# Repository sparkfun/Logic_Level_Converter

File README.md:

**NOTE:** *This product has been retired from our catalog. For a more up-to-date version, try looking at the [bi-directional logic level converter](https://www.sparkfun.com/products/12009).*

*If you are looking for more up-to-date info, please check out some of these resources to see how other users are still hacking and improving on this product.*

* *[SparkFun Forum](https://forum.sparkfun.com/)*
* *[Comments Here on GitHub](https://github.com/sparkfun/Logic_Level_Converter/issues)*
* *[IRC Channel](https://www.sparkfun.com/news/263)*

Logic Level Converter
=====================

[*Logic Level Converter*](https://www.sparkfun.com/products/11978)

Design files for the [Logic Level Converter board](https://www.sparkfun.com/products/11978).

Repository Contents
-------------------

* **/hardware** - Eagle PCB layout files
* **/Production Files** - Files to support SparkFun production

Documentation
--------------
* **[Hookup Guide](https://learn.sparkfun.com/tutorials/retired---using-the-logic-level-converter)** - Basic hookup guide

License Information
-------------------

All contents of this repository are released under [Creative Commons Share-alike 3.0](http://creativecommons.org/licenses/by-sa/3.0/).

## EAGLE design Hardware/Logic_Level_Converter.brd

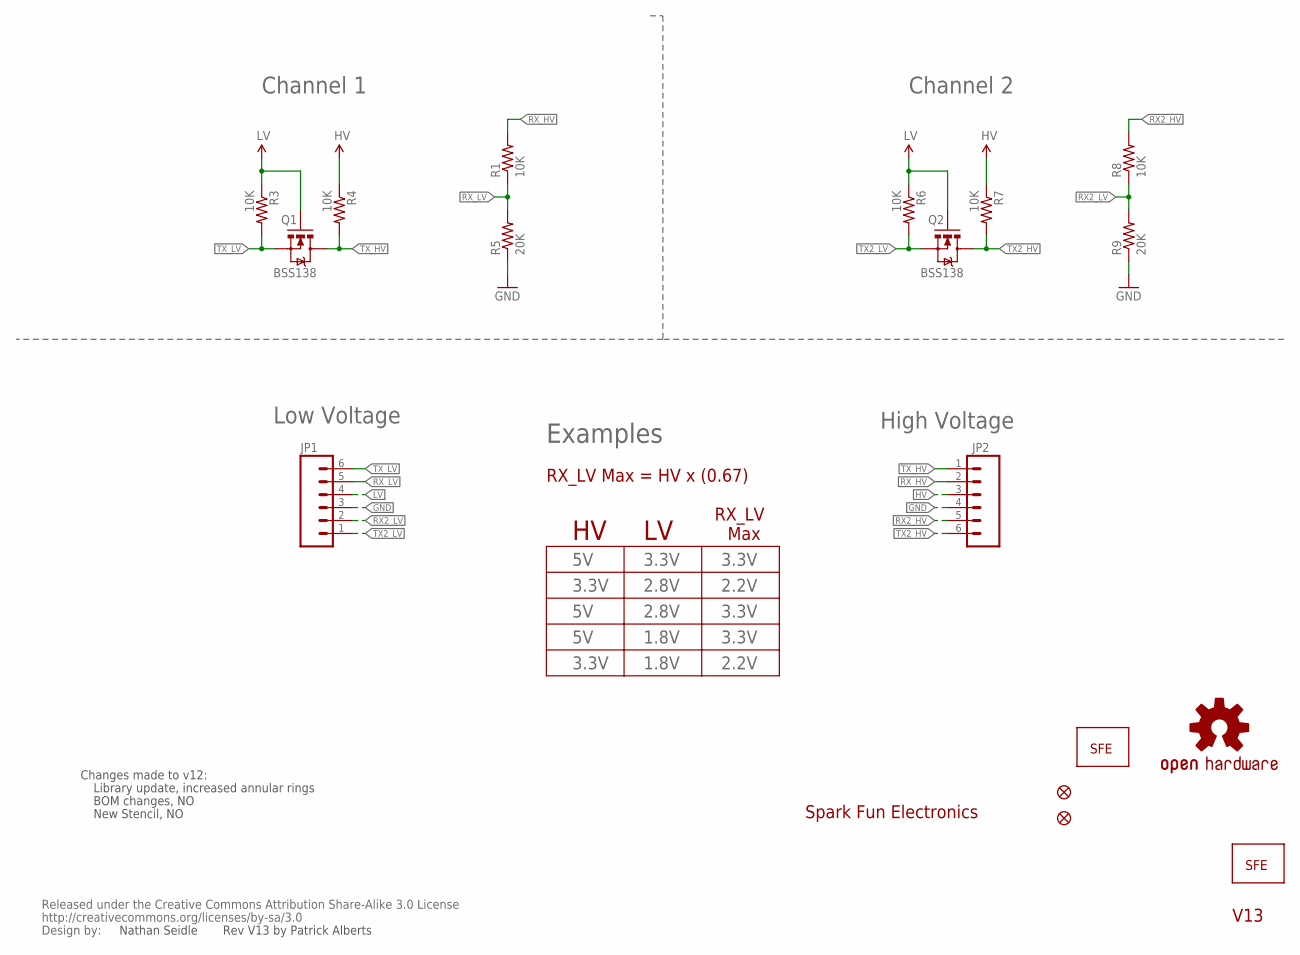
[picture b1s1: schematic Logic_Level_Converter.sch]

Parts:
CC_TEXT1: CREATIVE_COMMONS
JP1, JP2: M06SIP; 1X06
JP3, JP4: FIDUCIALUFIDUCIAL; MICRO-FIDUCIAL
JP5: LOGO-SFENW2; SFE-NEW-WEB
Q1, Q2: BSS138; SOT23-3
R1, R3, R4, R6, R7, R8: 10K; 0603-RES
R5, R9: 20K; 0603-RES
U$1: LOGO-SFESK; SFE-LOGO-FLAME
U$2: OSHW-LOGOS; OSHW-LOGO-S

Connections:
GND: JP1.3, JP2.4, R5.1, R9.1
HV: JP2.3, R4.1, R7.1
LV: JP1.4, Q1.1 (G), Q2.1 (G), R3.1, R6.1
RX2_HV: JP2.5, R8.2
RX2_LV: JP1.2, R8.1, R9.2
RX_HV: JP2.2, R1.2
RX_LV: JP1.5, R1.1, R5.2
TX2_HV: JP2.6, Q2.3 (D), R7.2
TX2_LV: JP1.1, Q2.2 (S), R6.2
TX_HV: JP2.1, Q1.3 (D), R4.2
TX_LV: JP1.6, Q1.2 (S), R3.2

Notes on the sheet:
Spark Fun Electronics
Channel 1
Channel 2
High Voltage
Low Voltage
Examples
RX_LV
Max
3.3V
2.8V
2.2V
1.8V
Changes made to v12:
Library update, increased annular rings
BOM changes, NO
New Stencil, NO
V13
RX_LV Max = HV x (0.67)
Nathan Seidle
Rev V13 by Patrick Alberts

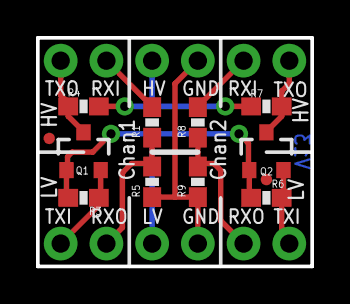
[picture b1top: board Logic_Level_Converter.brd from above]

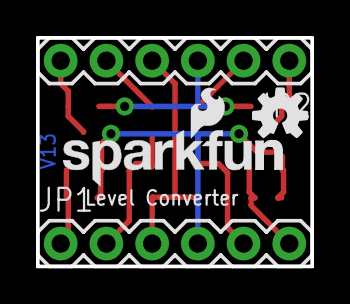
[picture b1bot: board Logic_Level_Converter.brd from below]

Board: 2 copper layers, 15.2 x 12.7 mm, 18 parts (5 on the bottom side), 11 nets.

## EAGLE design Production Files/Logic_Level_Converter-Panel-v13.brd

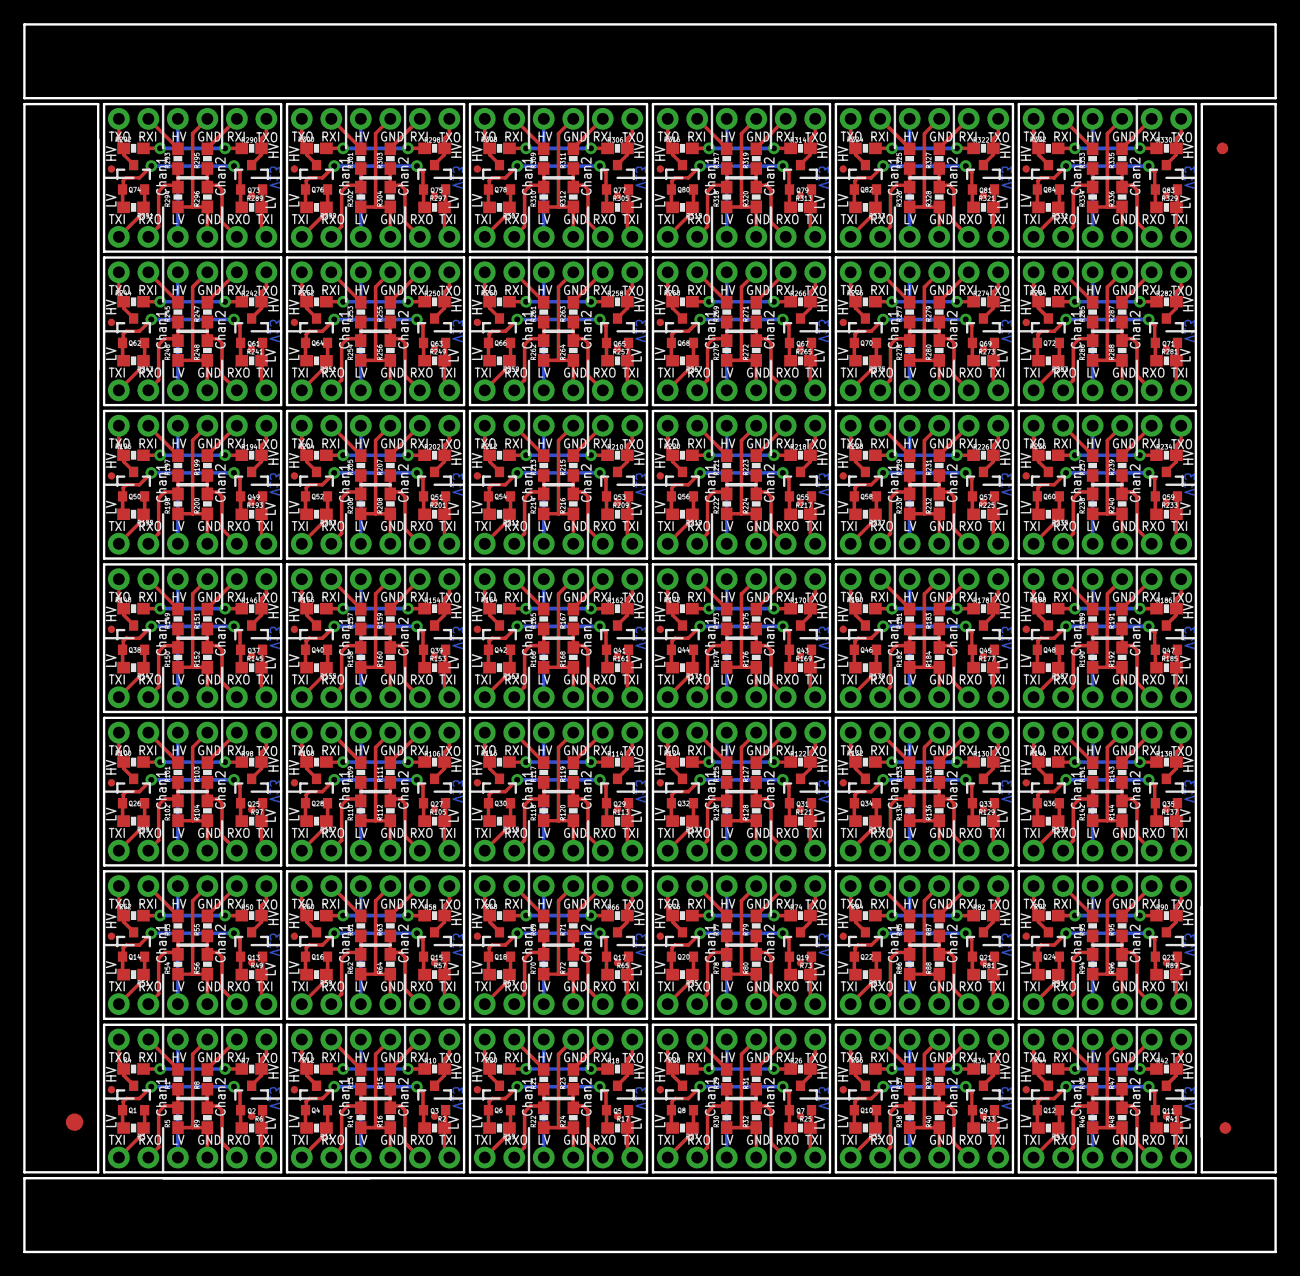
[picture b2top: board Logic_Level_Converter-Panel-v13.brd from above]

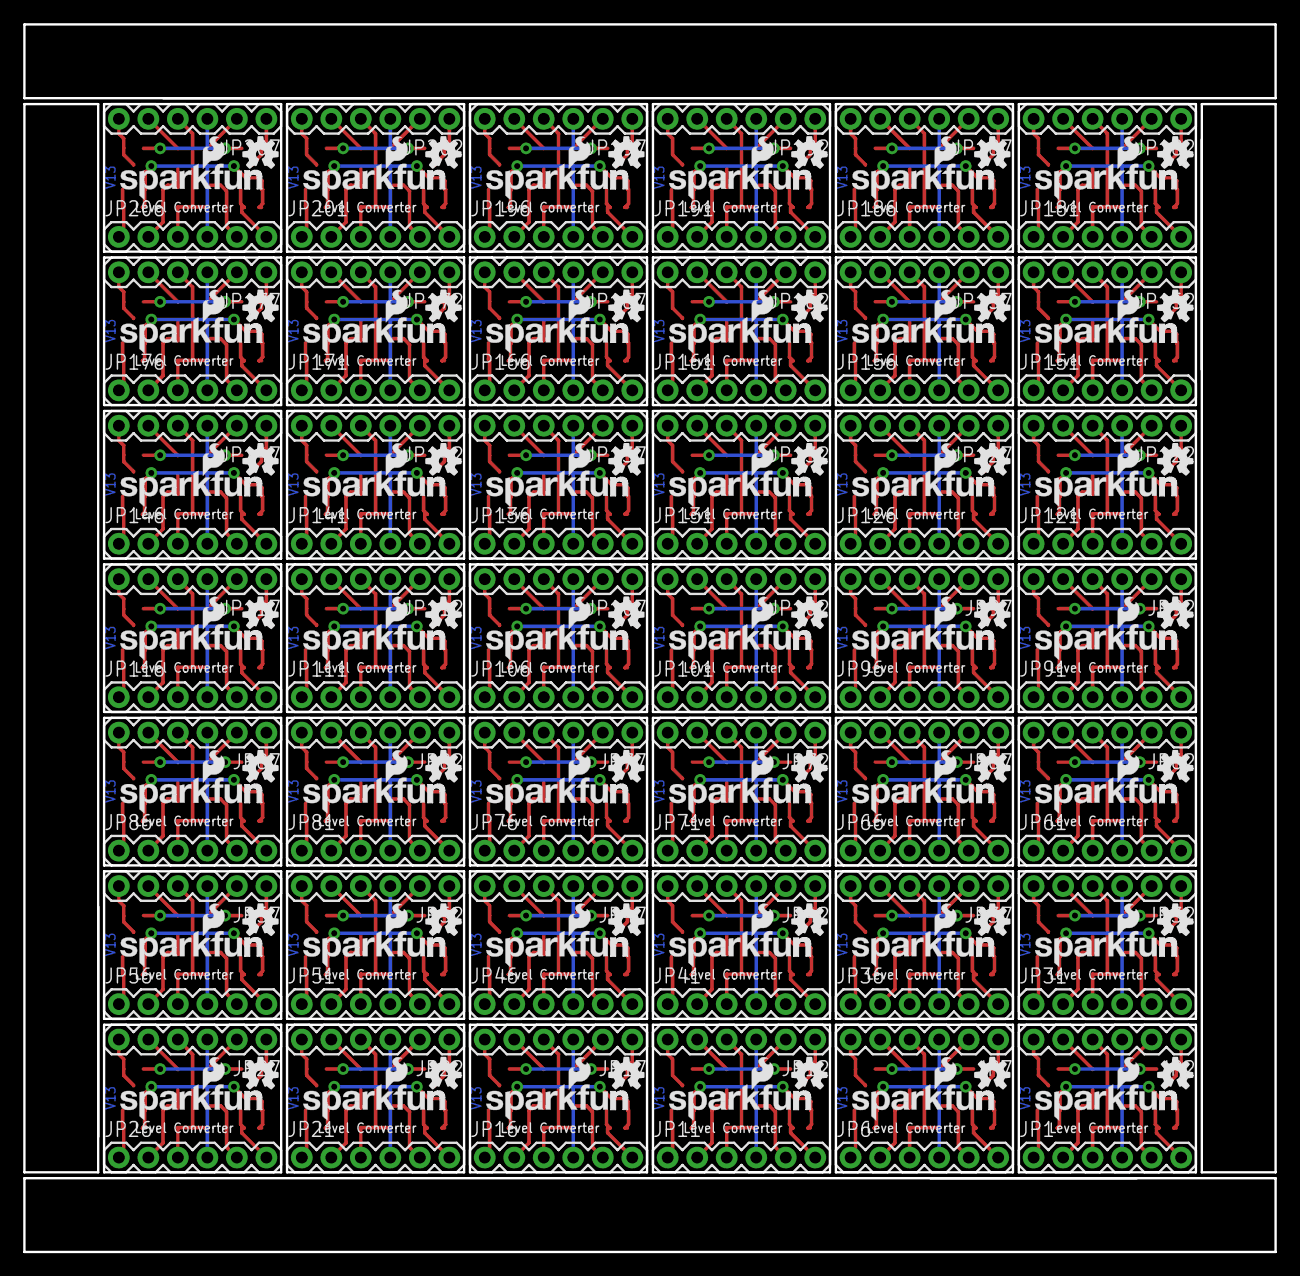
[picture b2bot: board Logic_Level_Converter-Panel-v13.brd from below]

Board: 2 copper layers, 107.7 x 105.7 mm, 717 parts (210 on the bottom side), 462 nets.

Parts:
E$1: FIDUCIAL-1.5X3
E$4, E$5: FIDUCIAL-1X2
JP1, JP2, JP6, JP7, JP11, JP12, JP16, JP17, JP21, JP22, JP26, JP27, JP31, JP32, JP36, JP37, JP41, JP42, JP46, JP47, JP51, JP52, JP56, JP57, JP61, JP62, JP66, JP67, JP71, JP72, JP76, JP77, JP81, JP82, JP86, JP87, JP91, JP92, JP96, JP97, JP101, JP102, JP106, JP107, JP111, JP112, JP116, JP117, JP121, JP122, JP126, JP127, JP131, JP132, JP136, JP137, JP141, JP142, JP146, JP147, JP151, JP152, JP156, JP157, JP161, JP162, JP166, JP167, JP171, JP172, JP176, JP177, JP181, JP182, JP186, JP187, JP191, JP192, JP196, JP197, JP201, JP202, JP206, JP207: 1X06
JP3, JP4, JP8, JP9, JP13, JP14, JP18, JP19, JP23, JP24, JP28, JP29, JP33, JP34, JP38, JP39, JP43, JP44, JP48, JP49, JP53, JP54, JP58, JP59, JP63, JP64, JP68, JP69, JP73, JP74, JP78, JP79, JP83, JP84, JP88, JP89, JP93, JP94, JP98, JP99, JP103, JP104, JP108, JP109, JP113, JP114, JP118, JP119, JP123, JP124, JP128, JP129, JP133, JP134, JP138, JP139, JP143, JP144, JP148, JP149, JP153, JP154, JP158, JP159, JP163, JP164, JP168, JP169, JP173, JP174, JP178, JP179, JP183, JP184, JP188, JP189, JP193, JP194, JP198, JP199, JP203, JP204, JP208, JP209: FIDUCIALUFIDUCIAL; MICRO-FIDUCIAL
JP5, JP10, JP15, JP20, JP25, JP30, JP35, JP40, JP45, JP50, JP55, JP60, JP65, JP70, JP75, JP80, JP85, JP90, JP95, JP100, JP105, JP110, JP115, JP120, JP125, JP130, JP135, JP140, JP145, JP150, JP155, JP160, JP165, JP170, JP175, JP180, JP185, JP190, JP195, JP200, JP205, JP210: LOGO-SFENW2; SFE-NEW-WEB
Q1, Q2, Q3, Q4, Q5, Q6, Q7, Q8, Q9, Q10, Q11, Q12, Q13, Q14, Q15, Q16, Q17, Q18, Q19, Q20, Q21, Q22, Q23, Q24, Q25, Q26, Q27, Q28, Q29, Q30, Q31, Q32, Q33, Q34, Q35, Q36, Q37, Q38, Q39, Q40, Q41, Q42, Q43, Q44, Q45, Q46, Q47, Q48, Q49, Q50, Q51, Q52, Q53, Q54, Q55, Q56, Q57, Q58, Q59, Q60, Q61, Q62, Q63, Q64, Q65, Q66, Q67, Q68, Q69, Q70, Q71, Q72, Q73, Q74, Q75, Q76, Q77, Q78, Q79, Q80, Q81, Q82, Q83, Q84: BSS138; SOT23-3
R1, R2, R3, R4, R6, R7, R8, R10, R11, R12, R13, R15, R17, R18, R19, R20, R21, R23, R25, R26, R27, R28, R29, R31, R33, R34, R35, R36, R37, R39, R41, R42, R43, R44, R45, R47, R49, R50, R51, R52, R53, R55, R57, R58, R59, R60, R61, R63, R65, R66, R67, R68, R69, R71, R73, R74, R75, R76, R77, R79, R81, R82, R83, R84, R85, R87, R89, R90, R91, R92, R93, R95, R97, R98, R99, R100, R101, R103, R105, R106, R107, R108, R109, R111, R113, R114, R115, R116, R117, R119, R121, R122, R123, R124, R125, R127, R129, R130, R131, R132, R133, R135, R137, R138, R139, R140, R141, R143, R145, R146, R147, R148, R149, R151, R153, R154, R155, R156, R157, R159, R161, R162, R163, R164, R165, R167, R169, R170, R171, R172, R173, R175, R177, R178, R179, R180, R181, R183, R185, R186, R187, R188, R189, R191, R193, R194, R195, R196, R197, R199, R201, R202, R203, R204, R205, R207, R209, R210, R211, R212, R213, R215, R217, R218, R219, R220, R221, R223, R225, R226, R227, R228, R229, R231, R233, R234, R235, R236, R237, R239, R241, R242, R243, R244, R245, R247, R249, R250, R251, R252, R253, R255, R257, R258, R259, R260, R261, R263, R265, R266, R267, R268, R269, R271, R273, R274, R275, R276, R277, R279, R281, R282, R283, R284, R285, R287, R289, R290, R291, R292, R293, R295, R297, R298, R299, R300, R301, R303, R305, R306, R307, R308, R309, R311, R313, R314, R315, R316, R317, R319, R321, R322, R323, R324, R325, R327, R329, R330, R331, R332, R333, R335: 10K; 0603-RES
R5, R9, R14, R16, R22, R24, R30, R32, R38, R40, R46, R48, R54, R56, R62, R64, R70, R72, R78, R80, R86, R88, R94, R96, R102, R104, R110, R112, R118, R120, R126, R128, R134, R136, R142, R144, R150, R152, R158, R160, R166, R168, R174, R176, R182, R184, R190, R192, R198, R200, R206, R208, R214, R216, R222, R224, R230, R232, R238, R240, R246, R248, R254, R256, R262, R264, R270, R272, R278, R280, R286, R288, R294, R296, R302, R304, R310, R312, R318, R320, R326, R328, R334, R336: 20K; 0603-RES
U$1, U$3, U$5, U$7, U$9, U$11, U$13, U$15, U$17, U$19, U$21, U$23, U$25, U$27, U$29, U$31, U$33, U$35, U$37, U$39, U$41, U$43, U$45, U$47, U$49, U$51, U$53, U$55, U$57, U$59, U$61, U$63, U$65, U$67, U$69, U$71, U$73, U$75, U$77, U$79, U$81, U$83: LOGO-SFESK; SFE-LOGO-FLAME
U$2, U$4, U$6, U$8, U$10, U$12, U$14, U$16, U$18, U$20, U$22, U$24, U$26, U$28, U$30, U$32, U$34, U$36, U$38, U$40, U$42, U$44, U$46, U$48, U$50, U$52, U$54, U$56, U$58, U$60, U$62, U$64, U$66, U$68, U$70, U$72, U$74, U$76, U$78, U$80, U$82, U$84: OSHW-LOGOS; OSHW-LOGO-S

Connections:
GND: JP1.3, JP2.4, R5.1, R9.1
GND1: JP6.3, JP7.4, R14.1, R16.1
GND2: JP11.3, JP12.4, R22.1, R24.1
GND3: JP16.3, JP17.4, R30.1, R32.1
GND4: JP21.3, JP22.4, R38.1, R40.1
GND5: JP26.3, JP27.4, R46.1, R48.1
GND6: JP31.3, JP32.4, R54.1, R56.1
GND7: JP36.3, JP37.4, R62.1, R64.1
GND8: JP41.3, JP42.4, R70.1, R72.1
GND9: JP46.3, JP47.4, R78.1, R80.1
GND10: JP51.3, JP52.4, R86.1, R88.1
GND11: JP56.3, JP57.4, R94.1, R96.1
GND12: JP61.3, JP62.4, R102.1, R104.1
GND13: JP66.3, JP67.4, R110.1, R112.1
GND14: JP71.3, JP72.4, R118.1, R120.1
GND15: JP76.3, JP77.4, R126.1, R128.1
GND16: JP81.3, JP82.4, R134.1, R136.1
GND17: JP86.3, JP87.4, R142.1, R144.1
GND18: JP91.3, JP92.4, R150.1, R152.1
GND19: JP96.3, JP97.4, R158.1, R160.1
GND20: JP101.3, JP102.4, R166.1, R168.1
GND21: JP106.3, JP107.4, R174.1, R176.1
GND22: JP111.3, JP112.4, R182.1, R184.1
GND23: JP116.3, JP117.4, R190.1, R192.1
GND24: JP121.3, JP122.4, R198.1, R200.1
GND25: JP126.3, JP127.4, R206.1, R208.1
GND26: JP131.3, JP132.4, R214.1, R216.1
GND27: JP136.3, JP137.4, R222.1, R224.1
GND28: JP141.3, JP142.4, R230.1, R232.1
GND29: JP146.3, JP147.4, R238.1, R240.1
GND30: JP151.3, JP152.4, R246.1, R248.1
GND31: JP156.3, JP157.4, R254.1, R256.1
GND32: JP161.3, JP162.4, R262.1, R264.1
GND33: JP166.3, JP167.4, R270.1, R272.1
GND34: JP171.3, JP172.4, R278.1, R280.1
GND35: JP176.3, JP177.4, R286.1, R288.1
GND36: JP181.3, JP182.4, R294.1, R296.1
GND37: JP186.3, JP187.4, R302.1, R304.1
GND38: JP191.3, JP192.4, R310.1, R312.1
GND39: JP196.3, JP197.4, R318.1, R320.1
GND40: JP201.3, JP202.4, R326.1, R328.1
GND41: JP206.3, JP207.4, R334.1, R336.1
HV: JP2.3, R4.1, R7.1
HV1: JP7.3, R10.1, R12.1
HV2: JP12.3, R18.1, R20.1
HV3: JP17.3, R26.1, R28.1
HV4: JP22.3, R34.1, R36.1
HV5: JP27.3, R42.1, R44.1
HV6: JP32.3, R50.1, R52.1
HV7: JP37.3, R58.1, R60.1
HV8: JP42.3, R66.1, R68.1
HV9: JP47.3, R74.1, R76.1
HV10: JP52.3, R82.1, R84.1
HV11: JP57.3, R90.1, R92.1
HV12: JP62.3, R98.1, R100.1
HV13: JP67.3, R106.1, R108.1
HV14: JP72.3, R114.1, R116.1
HV15: JP77.3, R122.1, R124.1
HV16: JP82.3, R130.1, R132.1
HV17: JP87.3, R138.1, R140.1
HV18: JP92.3, R146.1, R148.1
HV19: JP97.3, R154.1, R156.1
HV20: JP102.3, R162.1, R164.1
HV21: JP107.3, R170.1, R172.1
HV22: JP112.3, R178.1, R180.1
HV23: JP117.3, R186.1, R188.1
HV24: JP122.3, R194.1, R196.1
HV25: JP127.3, R202.1, R204.1
HV26: JP132.3, R210.1, R212.1
HV27: JP137.3, R218.1, R220.1
HV28: JP142.3, R226.1, R228.1
HV29: JP147.3, R234.1, R236.1
HV30: JP152.3, R242.1, R244.1
HV31: JP157.3, R250.1, R252.1
HV32: JP162.3, R258.1, R260.1
HV33: JP167.3, R266.1, R268.1
HV34: JP172.3, R274.1, R276.1
HV35: JP177.3, R282.1, R284.1
HV36: JP182.3, R290.1, R292.1
HV37: JP187.3, R298.1, R300.1
HV38: JP192.3, R306.1, R308.1
HV39: JP197.3, R314.1, R316.1
HV40: JP202.3, R322.1, R324.1
HV41: JP207.3, R330.1, R332.1
LV: JP1.4, Q1.1, Q2.1, R3.1, R6.1
LV1: JP6.4, Q3.1, Q4.1, R2.1, R11.1
LV2: JP11.4, Q5.1, Q6.1, R17.1, R19.1
LV3: JP16.4, Q7.1, Q8.1, R25.1, R27.1
LV4: JP21.4, Q9.1, Q10.1, R33.1, R35.1
LV5: JP26.4, Q11.1, Q12.1, R41.1, R43.1
LV6: JP31.4, Q13.1, Q14.1, R49.1, R51.1
LV7: JP36.4, Q15.1, Q16.1, R57.1, R59.1
LV8: JP41.4, Q17.1, Q18.1, R65.1, R67.1
LV9: JP46.4, Q19.1, Q20.1, R73.1, R75.1
LV10: JP51.4, Q21.1, Q22.1, R81.1, R83.1
LV11: JP56.4, Q23.1, Q24.1, R89.1, R91.1
LV12: JP61.4, Q25.1, Q26.1, R97.1, R99.1
LV13: JP66.4, Q27.1, Q28.1, R105.1, R107.1
LV14: JP71.4, Q29.1, Q30.1, R113.1, R115.1
LV15: JP76.4, Q31.1, Q32.1, R121.1, R123.1
LV16: JP81.4, Q33.1, Q34.1, R129.1, R131.1
LV17: JP86.4, Q35.1, Q36.1, R137.1, R139.1
LV18: JP91.4, Q37.1, Q38.1, R145.1, R147.1
LV19: JP96.4, Q39.1, Q40.1, R153.1, R155.1
LV20: JP101.4, Q41.1, Q42.1, R161.1, R163.1
LV21: JP106.4, Q43.1, Q44.1, R169.1, R171.1
LV22: JP111.4, Q45.1, Q46.1, R177.1, R179.1
LV23: JP116.4, Q47.1, Q48.1, R185.1, R187.1
LV24: JP121.4, Q49.1, Q50.1, R193.1, R195.1
LV25: JP126.4, Q51.1, Q52.1, R201.1, R203.1
LV26: JP131.4, Q53.1, Q54.1, R209.1, R211.1
LV27: JP136.4, Q55.1, Q56.1, R217.1, R219.1
LV28: JP141.4, Q57.1, Q58.1, R225.1, R227.1
LV29: JP146.4, Q59.1, Q60.1, R233.1, R235.1
LV30: JP151.4, Q61.1, Q62.1, R241.1, R243.1
LV31: JP156.4, Q63.1, Q64.1, R249.1, R251.1
LV32: JP161.4, Q65.1, Q66.1, R257.1, R259.1
LV33: JP166.4, Q67.1, Q68.1, R265.1, R267.1
LV34: JP171.4, Q69.1, Q70.1, R273.1, R275.1
LV35: JP176.4, Q71.1, Q72.1, R281.1, R283.1
LV36: JP181.4, Q73.1, Q74.1, R289.1, R291.1
LV37: JP186.4, Q75.1, Q76.1, R297.1, R299.1
LV38: JP191.4, Q77.1, Q78.1, R305.1, R307.1
LV39: JP196.4, Q79.1, Q80.1, R313.1, R315.1
LV40: JP201.4, Q81.1, Q82.1, R321.1, R323.1
LV41: JP206.4, Q83.1, Q84.1, R329.1, R331.1
RX2_HV: JP2.5, R8.2
RX2_HV1: JP7.5, R15.2
RX2_HV2: JP12.5, R23.2
RX2_HV3: JP17.5, R31.2
RX2_HV4: JP22.5, R39.2
RX2_HV5: JP27.5, R47.2
RX2_HV6: JP32.5, R55.2
RX2_HV7: JP37.5, R63.2
RX2_HV8: JP42.5, R71.2
RX2_HV9: JP47.5, R79.2
RX2_HV10: JP52.5, R87.2
RX2_HV11: JP57.5, R95.2
RX2_HV12: JP62.5, R103.2
RX2_HV13: JP67.5, R111.2
RX2_HV14: JP72.5, R119.2
RX2_HV15: JP77.5, R127.2
RX2_HV16: JP82.5, R135.2
RX2_HV17: JP87.5, R143.2
RX2_HV18: JP92.5, R151.2
RX2_HV19: JP97.5, R159.2
RX2_HV20: JP102.5, R167.2
RX2_HV21: JP107.5, R175.2
RX2_HV22: JP112.5, R183.2
RX2_HV23: JP117.5, R191.2
RX2_HV24: JP122.5, R199.2
RX2_HV25: JP127.5, R207.2
RX2_HV26: JP132.5, R215.2
RX2_HV27: JP137.5, R223.2
RX2_HV28: JP142.5, R231.2
RX2_HV29: JP147.5, R239.2
RX2_HV30: JP152.5, R247.2
RX2_HV31: JP157.5, R255.2
RX2_HV32: JP162.5, R263.2
RX2_HV33: JP167.5, R271.2
RX2_HV34: JP172.5, R279.2
RX2_HV35: JP177.5, R287.2
RX2_HV36: JP182.5, R295.2
RX2_HV37: JP187.5, R303.2
RX2_HV38: JP192.5, R311.2
RX2_HV39: JP197.5, R319.2
RX2_HV40: JP202.5, R327.2
RX2_HV41: JP207.5, R335.2
RX2_LV: JP1.2, R8.1, R9.2
RX2_LV1: JP6.2, R15.1, R16.2
RX2_LV2: JP11.2, R23.1, R24.2
RX2_LV3: JP16.2, R31.1, R32.2
RX2_LV4: JP21.2, R39.1, R40.2
RX2_LV5: JP26.2, R47.1, R48.2
RX2_LV6: JP31.2, R55.1, R56.2
RX2_LV7: JP36.2, R63.1, R64.2
RX2_LV8: JP41.2, R71.1, R72.2
RX2_LV9: JP46.2, R79.1, R80.2
RX2_LV10: JP51.2, R87.1, R88.2
RX2_LV11: JP56.2, R95.1, R96.2
RX2_LV12: JP61.2, R103.1, R104.2
RX2_LV13: JP66.2, R111.1, R112.2
RX2_LV14: JP71.2, R119.1, R120.2
RX2_LV15: JP76.2, R127.1, R128.2
RX2_LV16: JP81.2, R135.1, R136.2
RX2_LV17: JP86.2, R143.1, R144.2
RX2_LV18: JP91.2, R151.1, R152.2
RX2_LV19: JP96.2, R159.1, R160.2
RX2_LV20: JP101.2, R167.1, R168.2
RX2_LV21: JP106.2, R175.1, R176.2
RX2_LV22: JP111.2, R183.1, R184.2
RX2_LV23: JP116.2, R191.1, R192.2
RX2_LV24: JP121.2, R199.1, R200.2
RX2_LV25: JP126.2, R207.1, R208.2
RX2_LV26: JP131.2, R215.1, R216.2
RX2_LV27: JP136.2, R223.1, R224.2
RX2_LV28: JP141.2, R231.1, R232.2
RX2_LV29: JP146.2, R239.1, R240.2
RX2_LV30: JP151.2, R247.1, R248.2
RX2_LV31: JP156.2, R255.1, R256.2
RX2_LV32: JP161.2, R263.1, R264.2
RX2_LV33: JP166.2, R271.1, R272.2
RX2_LV34: JP171.2, R279.1, R280.2
RX2_LV35: JP176.2, R287.1, R288.2
RX2_LV36: JP181.2, R295.1, R296.2
RX2_LV37: JP186.2, R303.1, R304.2
RX2_LV38: JP191.2, R311.1, R312.2
RX2_LV39: JP196.2, R319.1, R320.2
RX2_LV40: JP201.2, R327.1, R328.2
RX2_LV41: JP206.2, R335.1, R336.2
RX_HV: JP2.2, R1.2
RX_HV1: JP7.2, R13.2
RX_HV2: JP12.2, R21.2
RX_HV3: JP17.2, R29.2
RX_HV4: JP22.2, R37.2
RX_HV5: JP27.2, R45.2
RX_HV6: JP32.2, R53.2
RX_HV7: JP37.2, R61.2
RX_HV8: JP42.2, R69.2
RX_HV9: JP47.2, R77.2
RX_HV10: JP52.2, R85.2
RX_HV11: JP57.2, R93.2
RX_HV12: JP62.2, R101.2
RX_HV13: JP67.2, R109.2
RX_HV14: JP72.2, R117.2
RX_HV15: JP77.2, R125.2
RX_HV16: JP82.2, R133.2
RX_HV17: JP87.2, R141.2
RX_HV18: JP92.2, R149.2
RX_HV19: JP97.2, R157.2
RX_HV20: JP102.2, R165.2
RX_HV21: JP107.2, R173.2
RX_HV22: JP112.2, R181.2
RX_HV23: JP117.2, R189.2
RX_HV24: JP122.2, R197.2
RX_HV25: JP127.2, R205.2
RX_HV26: JP132.2, R213.2
RX_HV27: JP137.2, R221.2
RX_HV28: JP142.2, R229.2
RX_HV29: JP147.2, R237.2
RX_HV30: JP152.2, R245.2
RX_HV31: JP157.2, R253.2
RX_HV32: JP162.2, R261.2
RX_HV33: JP167.2, R269.2
RX_HV34: JP172.2, R277.2
RX_HV35: JP177.2, R285.2
RX_HV36: JP182.2, R293.2
RX_HV37: JP187.2, R301.2
RX_HV38: JP192.2, R309.2
RX_HV39: JP197.2, R317.2
RX_HV40: JP202.2, R325.2
RX_HV41: JP207.2, R333.2
RX_LV: JP1.5, R1.1, R5.2
RX_LV1: JP6.5, R13.1, R14.2
RX_LV2: JP11.5, R21.1, R22.2
RX_LV3: JP16.5, R29.1, R30.2
RX_LV4: JP21.5, R37.1, R38.2
RX_LV5: JP26.5, R45.1, R46.2
RX_LV6: JP31.5, R53.1, R54.2
RX_LV7: JP36.5, R61.1, R62.2
RX_LV8: JP41.5, R69.1, R70.2
RX_LV9: JP46.5, R77.1, R78.2
RX_LV10: JP51.5, R85.1, R86.2
RX_LV11: JP56.5, R93.1, R94.2
RX_LV12: JP61.5, R101.1, R102.2
RX_LV13: JP66.5, R109.1, R110.2
RX_LV14: JP71.5, R117.1, R118.2
RX_LV15: JP76.5, R125.1, R126.2
RX_LV16: JP81.5, R133.1, R134.2
RX_LV17: JP86.5, R141.1, R142.2
RX_LV18: JP91.5, R149.1, R150.2
RX_LV19: JP96.5, R157.1, R158.2
RX_LV20: JP101.5, R165.1, R166.2
RX_LV21: JP106.5, R173.1, R174.2
RX_LV22: JP111.5, R181.1, R182.2
RX_LV23: JP116.5, R189.1, R190.2
RX_LV24: JP121.5, R197.1, R198.2
RX_LV25: JP126.5, R205.1, R206.2
RX_LV26: JP131.5, R213.1, R214.2
RX_LV27: JP136.5, R221.1, R222.2
RX_LV28: JP141.5, R229.1, R230.2
RX_LV29: JP146.5, R237.1, R238.2
RX_LV30: JP151.5, R245.1, R246.2
RX_LV31: JP156.5, R253.1, R254.2
RX_LV32: JP161.5, R261.1, R262.2
RX_LV33: JP166.5, R269.1, R270.2
RX_LV34: JP171.5, R277.1, R278.2
RX_LV35: JP176.5, R285.1, R286.2
RX_LV36: JP181.5, R293.1, R294.2
RX_LV37: JP186.5, R301.1, R302.2
RX_LV38: JP191.5, R309.1, R310.2
RX_LV39: JP196.5, R317.1, R318.2
RX_LV40: JP201.5, R325.1, R326.2
RX_LV41: JP206.5, R333.1, R334.2
TX2_HV: JP2.6, Q2.3, R7.2
TX2_HV1: JP7.6, Q3.3, R10.2
TX2_HV2: JP12.6, Q5.3, R18.2
TX2_HV3: JP17.6, Q7.3, R26.2
TX2_HV4: JP22.6, Q9.3, R34.2
TX2_HV5: JP27.6, Q11.3, R42.2
TX2_HV6: JP32.6, Q13.3, R50.2
TX2_HV7: JP37.6, Q15.3, R58.2
TX2_HV8: JP42.6, Q17.3, R66.2
TX2_HV9: JP47.6, Q19.3, R74.2
TX2_HV10: JP52.6, Q21.3, R82.2
TX2_HV11: JP57.6, Q23.3, R90.2
TX2_HV12: JP62.6, Q25.3, R98.2
TX2_HV13: JP67.6, Q27.3, R106.2
TX2_HV14: JP72.6, Q29.3, R114.2
TX2_HV15: JP77.6, Q31.3, R122.2
TX2_HV16: JP82.6, Q33.3, R130.2
TX2_HV17: JP87.6, Q35.3, R138.2
TX2_HV18: JP92.6, Q37.3, R146.2
TX2_HV19: JP97.6, Q39.3, R154.2
TX2_HV20: JP102.6, Q41.3, R162.2
TX2_HV21: JP107.6, Q43.3, R170.2
TX2_HV22: JP112.6, Q45.3, R178.2
TX2_HV23: JP117.6, Q47.3, R186.2
TX2_HV24: JP122.6, Q49.3, R194.2
TX2_HV25: JP127.6, Q51.3, R202.2
TX2_HV26: JP132.6, Q53.3, R210.2
TX2_HV27: JP137.6, Q55.3, R218.2
TX2_HV28: JP142.6, Q57.3, R226.2
TX2_HV29: JP147.6, Q59.3, R234.2
TX2_HV30: JP152.6, Q61.3, R242.2
TX2_HV31: JP157.6, Q63.3, R250.2
TX2_HV32: JP162.6, Q65.3, R258.2
TX2_HV33: JP167.6, Q67.3, R266.2
TX2_HV34: JP172.6, Q69.3, R274.2
TX2_HV35: JP177.6, Q71.3, R282.2
TX2_HV36: JP182.6, Q73.3, R290.2
TX2_HV37: JP187.6, Q75.3, R298.2
TX2_HV38: JP192.6, Q77.3, R306.2
TX2_HV39: JP197.6, Q79.3, R314.2
TX2_HV40: JP202.6, Q81.3, R322.2
TX2_HV41: JP207.6, Q83.3, R330.2
TX2_LV: JP1.1, Q2.2, R6.2
TX2_LV1: JP6.1, Q3.2, R2.2
TX2_LV2: JP11.1, Q5.2, R17.2
TX2_LV3: JP16.1, Q7.2, R25.2
TX2_LV4: JP21.1, Q9.2, R33.2
TX2_LV5: JP26.1, Q11.2, R41.2
TX2_LV6: JP31.1, Q13.2, R49.2
TX2_LV7: JP36.1, Q15.2, R57.2
TX2_LV8: JP41.1, Q17.2, R65.2
TX2_LV9: JP46.1, Q19.2, R73.2
TX2_LV10: JP51.1, Q21.2, R81.2
TX2_LV11: JP56.1, Q23.2, R89.2
TX2_LV12: JP61.1, Q25.2, R97.2
TX2_LV13: JP66.1, Q27.2, R105.2
TX2_LV14: JP71.1, Q29.2, R113.2
TX2_LV15: JP76.1, Q31.2, R121.2
TX2_LV16: JP81.1, Q33.2, R129.2
TX2_LV17: JP86.1, Q35.2, R137.2
TX2_LV18: JP91.1, Q37.2, R145.2
TX2_LV19: JP96.1, Q39.2, R153.2
TX2_LV20: JP101.1, Q41.2, R161.2
TX2_LV21: JP106.1, Q43.2, R169.2
TX2_LV22: JP111.1, Q45.2, R177.2
TX2_LV23: JP116.1, Q47.2, R185.2
TX2_LV24: JP121.1, Q49.2, R193.2
TX2_LV25: JP126.1, Q51.2, R201.2
TX2_LV26: JP131.1, Q53.2, R209.2
TX2_LV27: JP136.1, Q55.2, R217.2
TX2_LV28: JP141.1, Q57.2, R225.2
TX2_LV29: JP146.1, Q59.2, R233.2
TX2_LV30: JP151.1, Q61.2, R241.2
TX2_LV31: JP156.1, Q63.2, R249.2
TX2_LV32: JP161.1, Q65.2, R257.2
TX2_LV33: JP166.1, Q67.2, R265.2
TX2_LV34: JP171.1, Q69.2, R273.2
TX2_LV35: JP176.1, Q71.2, R281.2
TX2_LV36: JP181.1, Q73.2, R289.2
TX2_LV37: JP186.1, Q75.2, R297.2
TX2_LV38: JP191.1, Q77.2, R305.2
TX2_LV39: JP196.1, Q79.2, R313.2
TX2_LV40: JP201.1, Q81.2, R321.2
TX2_LV41: JP206.1, Q83.2, R329.2
TX_HV: JP2.1, Q1.3, R4.2
TX_HV1: JP7.1, Q4.3, R12.2
TX_HV2: JP12.1, Q6.3, R20.2
TX_HV3: JP17.1, Q8.3, R28.2
TX_HV4: JP22.1, Q10.3, R36.2
TX_HV5: JP27.1, Q12.3, R44.2
TX_HV6: JP32.1, Q14.3, R52.2
TX_HV7: JP37.1, Q16.3, R60.2
TX_HV8: JP42.1, Q18.3, R68.2
TX_HV9: JP47.1, Q20.3, R76.2
TX_HV10: JP52.1, Q22.3, R84.2
TX_HV11: JP57.1, Q24.3, R92.2
TX_HV12: JP62.1, Q26.3, R100.2
TX_HV13: JP67.1, Q28.3, R108.2
TX_HV14: JP72.1, Q30.3, R116.2
TX_HV15: JP77.1, Q32.3, R124.2
TX_HV16: JP82.1, Q34.3, R132.2
TX_HV17: JP87.1, Q36.3, R140.2
TX_HV18: JP92.1, Q38.3, R148.2
TX_HV19: JP97.1, Q40.3, R156.2
TX_HV20: JP102.1, Q42.3, R164.2
TX_HV21: JP107.1, Q44.3, R172.2
TX_HV22: JP112.1, Q46.3, R180.2
TX_HV23: JP117.1, Q48.3, R188.2
TX_HV24: JP122.1, Q50.3, R196.2
TX_HV25: JP127.1, Q52.3, R204.2
TX_HV26: JP132.1, Q54.3, R212.2
TX_HV27: JP137.1, Q56.3, R220.2
TX_HV28: JP142.1, Q58.3, R228.2
TX_HV29: JP147.1, Q60.3, R236.2
TX_HV30: JP152.1, Q62.3, R244.2
TX_HV31: JP157.1, Q64.3, R252.2
TX_HV32: JP162.1, Q66.3, R260.2
TX_HV33: JP167.1, Q68.3, R268.2
TX_HV34: JP172.1, Q70.3, R276.2
TX_HV35: JP177.1, Q72.3, R284.2
TX_HV36: JP182.1, Q74.3, R292.2
TX_HV37: JP187.1, Q76.3, R300.2
TX_HV38: JP192.1, Q78.3, R308.2
TX_HV39: JP197.1, Q80.3, R316.2
TX_HV40: JP202.1, Q82.3, R324.2
TX_HV41: JP207.1, Q84.3, R332.2
TX_LV: JP1.6, Q1.2, R3.2
TX_LV1: JP6.6, Q4.2, R11.2
TX_LV2: JP11.6, Q6.2, R19.2
TX_LV3: JP16.6, Q8.2, R27.2
TX_LV4: JP21.6, Q10.2, R35.2
TX_LV5: JP26.6, Q12.2, R43.2
TX_LV6: JP31.6, Q14.2, R51.2
TX_LV7: JP36.6, Q16.2, R59.2
TX_LV8: JP41.6, Q18.2, R67.2
TX_LV9: JP46.6, Q20.2, R75.2
TX_LV10: JP51.6, Q22.2, R83.2
TX_LV11: JP56.6, Q24.2, R91.2
TX_LV12: JP61.6, Q26.2, R99.2
TX_LV13: JP66.6, Q28.2, R107.2
TX_LV14: JP71.6, Q30.2, R115.2
TX_LV15: JP76.6, Q32.2, R123.2
TX_LV16: JP81.6, Q34.2, R131.2
TX_LV17: JP86.6, Q36.2, R139.2
TX_LV18: JP91.6, Q38.2, R147.2
TX_LV19: JP96.6, Q40.2, R155.2
TX_LV20: JP101.6, Q42.2, R163.2
TX_LV21: JP106.6, Q44.2, R171.2
TX_LV22: JP111.6, Q46.2, R179.2
TX_LV23: JP116.6, Q48.2, R187.2
TX_LV24: JP121.6, Q50.2, R195.2
TX_LV25: JP126.6, Q52.2, R203.2
TX_LV26: JP131.6, Q54.2, R211.2
TX_LV27: JP136.6, Q56.2, R219.2
TX_LV28: JP141.6, Q58.2, R227.2
TX_LV29: JP146.6, Q60.2, R235.2
TX_LV30: JP151.6, Q62.2, R243.2
TX_LV31: JP156.6, Q64.2, R251.2
TX_LV32: JP161.6, Q66.2, R259.2
TX_LV33: JP166.6, Q68.2, R267.2
TX_LV34: JP171.6, Q70.2, R275.2
TX_LV35: JP176.6, Q72.2, R283.2
TX_LV36: JP181.6, Q74.2, R291.2
TX_LV37: JP186.6, Q76.2, R299.2
TX_LV38: JP191.6, Q78.2, R307.2
TX_LV39: JP196.6, Q80.2, R315.2
TX_LV40: JP201.6, Q82.2, R323.2
TX_LV41: JP206.6, Q84.2, R331.2

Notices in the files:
parts and their libraries:
SparkFun-Aesthetics: Licensing: CC v3.0 Share-Alike You are welcome to use this library for commercial purposes.
SparkFun-Aesthetics: Released under the Creative Commons Attribution Share-Alike 3.0 License
SparkFun-Aesthetics: Creative Commons License summary
